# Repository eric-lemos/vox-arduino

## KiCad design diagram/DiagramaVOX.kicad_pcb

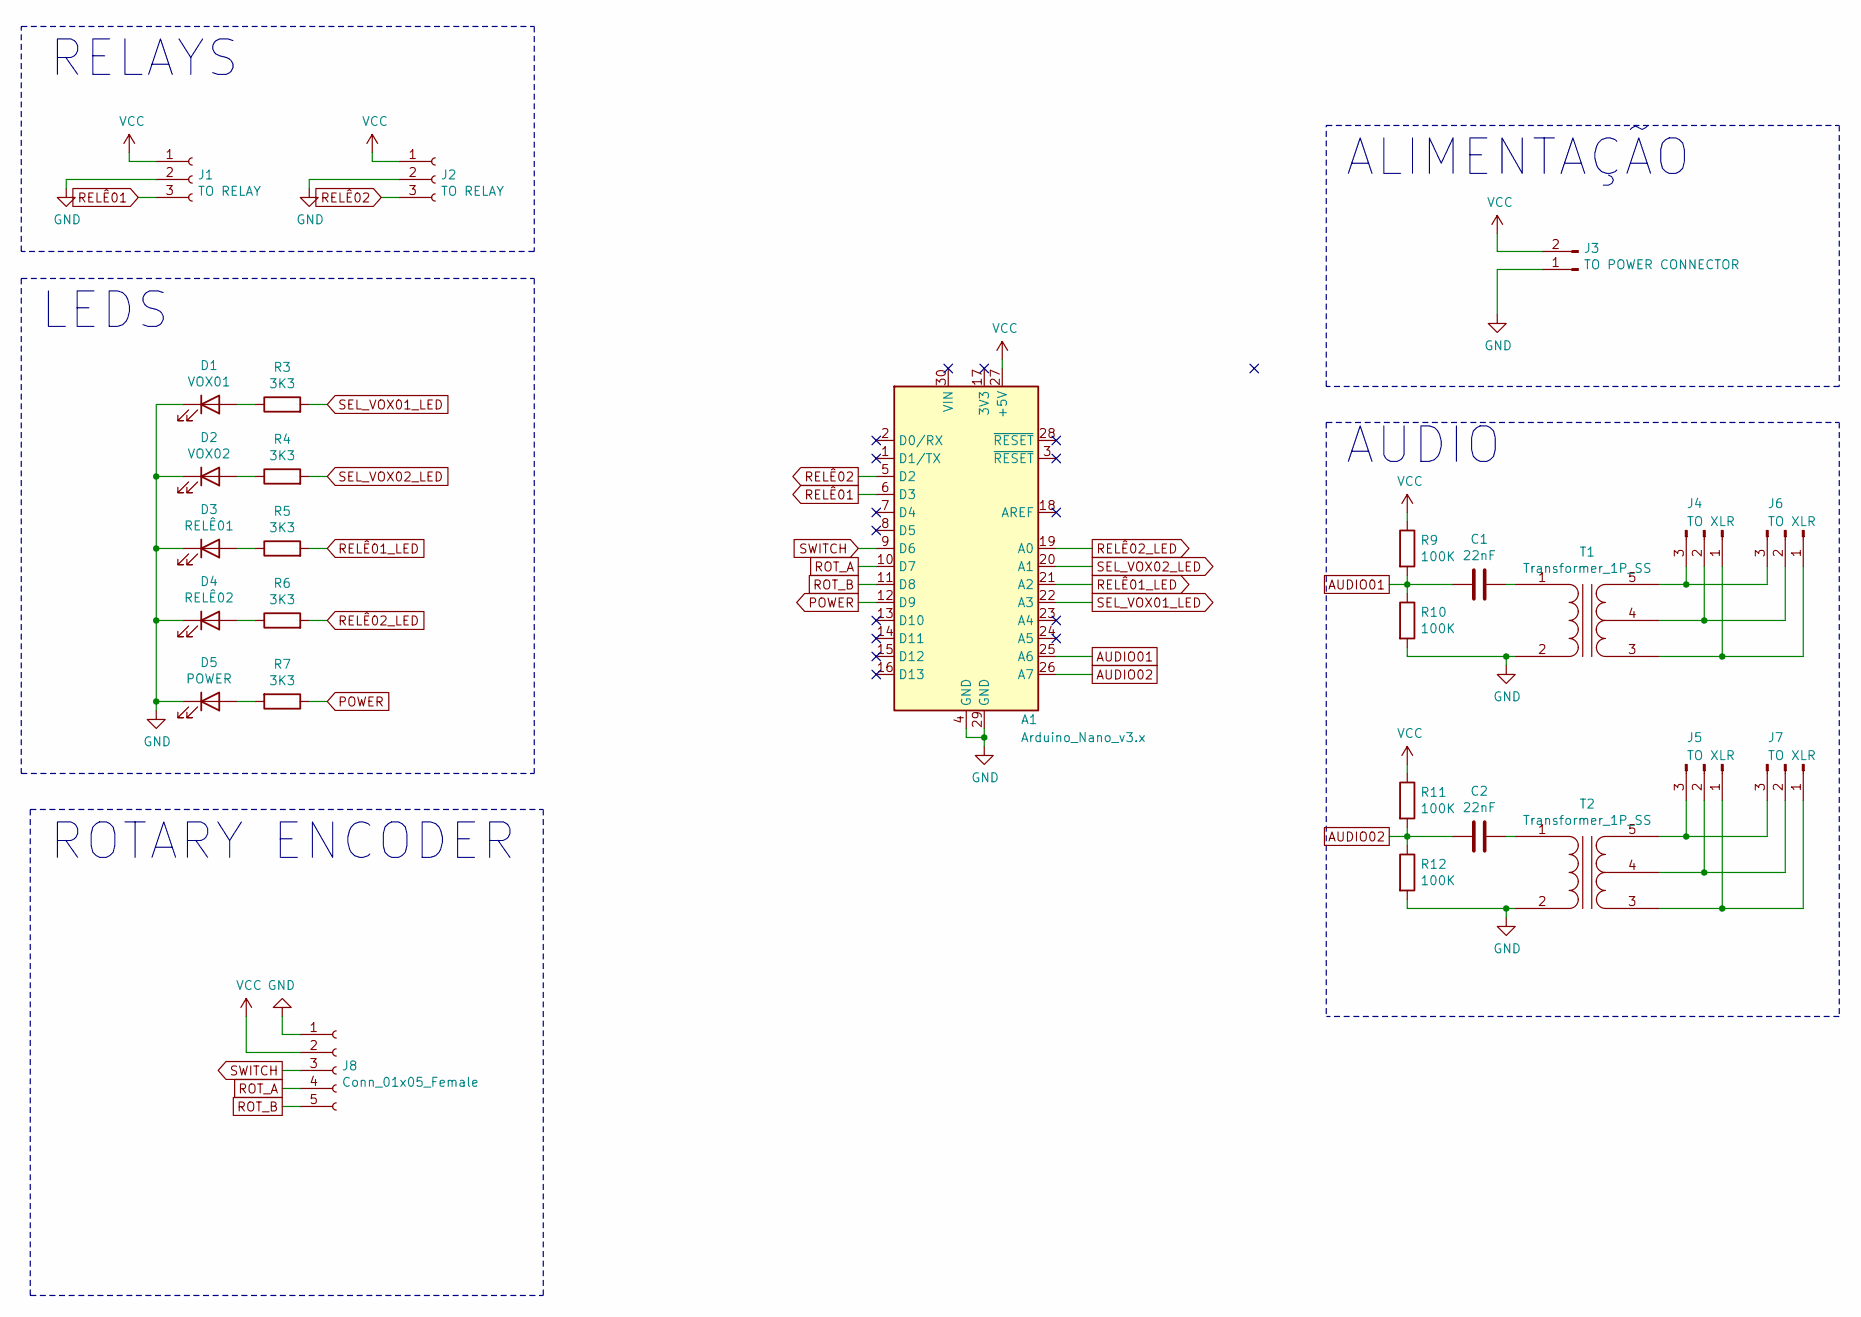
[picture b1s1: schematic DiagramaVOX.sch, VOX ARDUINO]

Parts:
A1: Arduino_Nano_v3.x; Arduino_Nano
C1, C2: 22nF; C_Disc_D3.0mm_W1.6mm_P2.50mm
D1: VOX01; LED_D3.0mm
D2: VOX02; LED_D3.0mm
D3: RELÊ01; LED_D3.0mm
D4: RELÊ02; LED_D3.0mm
D5: POWER; LED_D3.0mm
J1, J2: TO RELAY; PinSocket_1x03_P2.54mm_Vertical
J3: TO POWER CONNECTOR; Molex_KK-254_AE-6410-02A_1x02_P2.54mm_Vertical
J4, J5, J6, J7: TO XLR; Molex_KK-254_AE-6410-03A_1x03_P2.54mm_Vertical
J8: Conn_01x05_Female; PinSocket_1x05_P2.54mm_Vertical
R3, R4, R5, R6, R7: 3K3; R_Axial_DIN0204_L3.6mm_D1.6mm_P7.62mm_Horizontal
R9, R10, R11, R12: 100K; R_Axial_DIN0204_L3.6mm_D1.6mm_P7.62mm_Horizontal
T1, T2: Transformer_1P_SS; Transformer_Audio

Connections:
AUDIO01: A1.25 (A6), C1.2, R9.2, R10.1
AUDIO02: A1.26 (A7), C2.2, R11.2, R12.1
GND: A1.4 (GND), A1.29 (GND), D1.1 (K), D2.1 (K), D3.1 (K), D4.1 (K), D5.1 (K), J1.2, J2.2, J3.1, J8.1, R10.2, R12.2, T1.2 (AB), T2.2 (AB)
unnamed: C1.1, T1.1 (AA)
unnamed: C2.1, T2.1 (AA)
unnamed: D1.2 (A), R3.1
unnamed: D2.2 (A), R4.1
unnamed: D3.2 (A), R5.1
unnamed: D4.2 (A), R6.1
unnamed: D5.2 (A), R7.2
unnamed: J4.1, J6.1, T1.3 (SA)
unnamed: J4.2, J6.2, T1.4 (SC)
unnamed: J4.3, J6.3, T1.5 (SB)
unnamed: J5.1, J7.1, T2.3 (SA)
unnamed: J5.2, J7.2, T2.4 (SC)
unnamed: J5.3, J7.3, T2.5 (SB)
POWER: A1.12 (D9), R7.1
RELÊ01: A1.6 (D3), J1.3
RELÊ01_LED: A1.21 (A2), R5.2
RELÊ02: A1.5 (D2), J2.3
RELÊ02_LED: A1.19 (A0), R6.2
ROT_A: A1.10 (D7), J8.4
ROT_B: A1.11 (D8), J8.5
SEL_VOX01_LED: A1.22 (A3), R3.2
SEL_VOX02_LED: A1.20 (A1), R4.2
SWITCH: A1.9 (D6), J8.3
VCC: A1.27 (+5V), J1.1, J2.1, J3.2, J8.2, R9.1, R11.1

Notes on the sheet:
AUDIO
ALIMENTAÇÃO
ROTARY ENCODER
LEDS
RELAYS

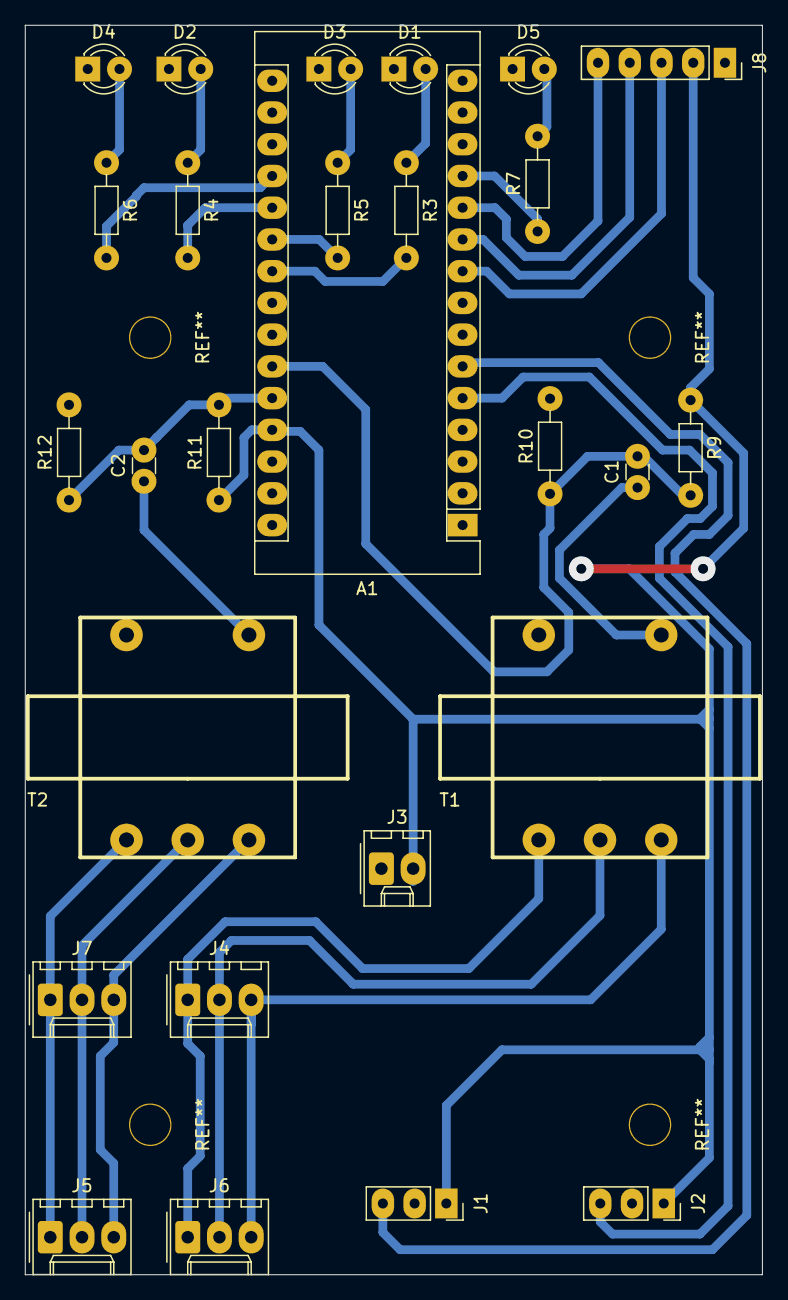
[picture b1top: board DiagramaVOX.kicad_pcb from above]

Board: 2 copper layers, 59.0 x 100.0 mm, 27 parts (0 on the bottom side), 27 nets.

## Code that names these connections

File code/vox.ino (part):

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const uint8_t LED_SYSTEM = 9;

//-------------------- ROTARY ---------------------|
const uint8_t SWITCH = 6;
const uint8_t ROT_A = 7;
const uint8_t ROT_B = 8;

//-------------------- CONFIG ---------------------|
const int PEAK_TIME = 40;
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
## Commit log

2021-10-28 VOX v1
